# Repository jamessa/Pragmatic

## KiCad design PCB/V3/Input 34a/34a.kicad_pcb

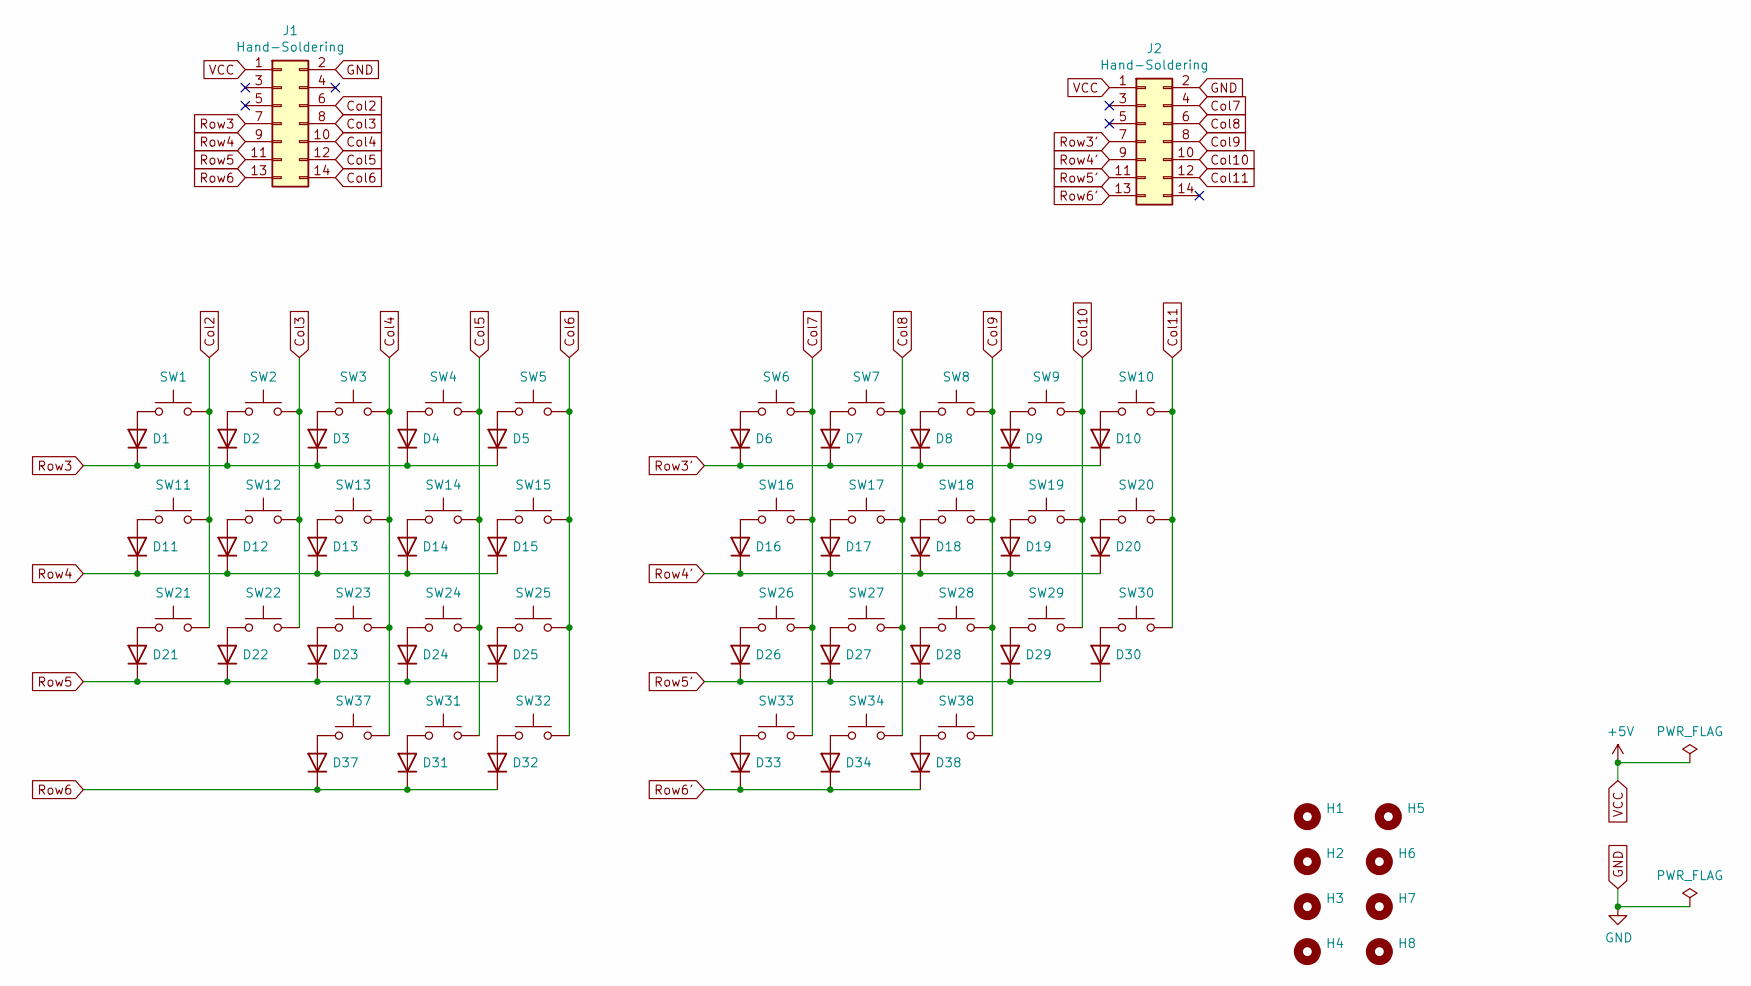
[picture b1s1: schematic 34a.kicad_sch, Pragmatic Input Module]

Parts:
D1, D2, D3, D4, D5, D6, D7, D8, D9, D10, D11, D12, D13, D14, D15, D16, D17, D18, D19, D20, D21, D22, D23, D24, D25, D26, D27, D28, D29, D30, D31, D32, D33, D34, D37, D38: 1N4148; D3_SMD_v2; LCSC C81598
H1, H2, H3, H4, H5, H6, H7, H8: MountingHole; MountingHole_2.5mm
J1, J2: Hand-Soldering; IDC-Header_2x07_P2.54mm_Vertical; LCSC C3406
SW1, SW2, SW3, SW4, SW5, SW6, SW7, SW8, SW9, SW10, SW11, SW12, SW13, SW14, SW15, SW16, SW17, SW18, SW19, SW20, SW21, SW22, SW23, SW24, SW25, SW26, SW27, SW28, SW29, SW30, SW31, SW32, SW33, SW34, SW37, SW38: SW_Push; MX_Hotswap

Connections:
Col2: J1.6, SW1.2, SW11.2, SW21.2
Col3: J1.8, SW2.2, SW12.2, SW22.2
Col4: J1.10, SW3.2, SW13.2, SW23.2, SW37.2
Col5: J1.12, SW4.2, SW14.2, SW24.2, SW31.2
Col6: J1.14, SW5.2, SW15.2, SW25.2, SW32.2
Col7: J2.4, SW6.2, SW16.2, SW26.2, SW33.2
Col8: J2.6, SW7.2, SW17.2, SW27.2, SW34.2
Col9: J2.8, SW8.2, SW18.2, SW28.2, SW38.2
Col10: J2.10, SW9.2, SW19.2, SW29.2
Col11: J2.12, SW10.2, SW20.2, SW30.2
GND: J1.2, J2.2
unnamed: D1.2 (A), SW1.1
unnamed: D2.2 (A), SW2.1
unnamed: D3.2 (A), SW3.1
unnamed: D4.2 (A), SW4.1
unnamed: D5.2 (A), SW5.1
unnamed: D6.2 (A), SW6.1
unnamed: D7.2 (A), SW7.1
unnamed: D8.2 (A), SW8.1
unnamed: D9.2 (A), SW9.1
unnamed: D10.2 (A), SW10.1
unnamed: D11.2 (A), SW11.1
unnamed: D12.2 (A), SW12.1
unnamed: D13.2 (A), SW13.1
unnamed: D14.2 (A), SW14.1
unnamed: D15.2 (A), SW15.1
unnamed: D16.2 (A), SW16.1
unnamed: D17.2 (A), SW17.1
unnamed: D18.2 (A), SW18.1
unnamed: D19.2 (A), SW19.1
unnamed: D20.2 (A), SW20.1
unnamed: D21.2 (A), SW21.1
unnamed: D22.2 (A), SW22.1
unnamed: D23.2 (A), SW23.1
unnamed: D24.2 (A), SW24.1
unnamed: D25.2 (A), SW25.1
unnamed: D26.2 (A), SW26.1
unnamed: D27.2 (A), SW27.1
unnamed: D28.2 (A), SW28.1
unnamed: D29.2 (A), SW29.1
unnamed: D30.2 (A), SW30.1
unnamed: D31.2 (A), SW31.1
unnamed: D32.2 (A), SW32.1
unnamed: D33.2 (A), SW33.1
unnamed: D34.2 (A), SW34.1
unnamed: D37.2 (A), SW37.1
unnamed: D38.2 (A), SW38.1
Row3: D1.1 (K), D2.1 (K), D3.1 (K), D4.1 (K), D5.1 (K), J1.7
Row3': D6.1 (K), D7.1 (K), D8.1 (K), D9.1 (K), D10.1 (K), J2.7
Row4: D11.1 (K), D12.1 (K), D13.1 (K), D14.1 (K), D15.1 (K), J1.9
Row4': D16.1 (K), D17.1 (K), D18.1 (K), D19.1 (K), D20.1 (K), J2.9
Row5: D21.1 (K), D22.1 (K), D23.1 (K), D24.1 (K), D25.1 (K), J1.11
Row5': D26.1 (K), D27.1 (K), D28.1 (K), D29.1 (K), D30.1 (K), J2.11
Row6: D31.1 (K), D32.1 (K), D37.1 (K), J1.13
Row6': D33.1 (K), D34.1 (K), D38.1 (K), J2.13
VCC: J1.1, J2.1

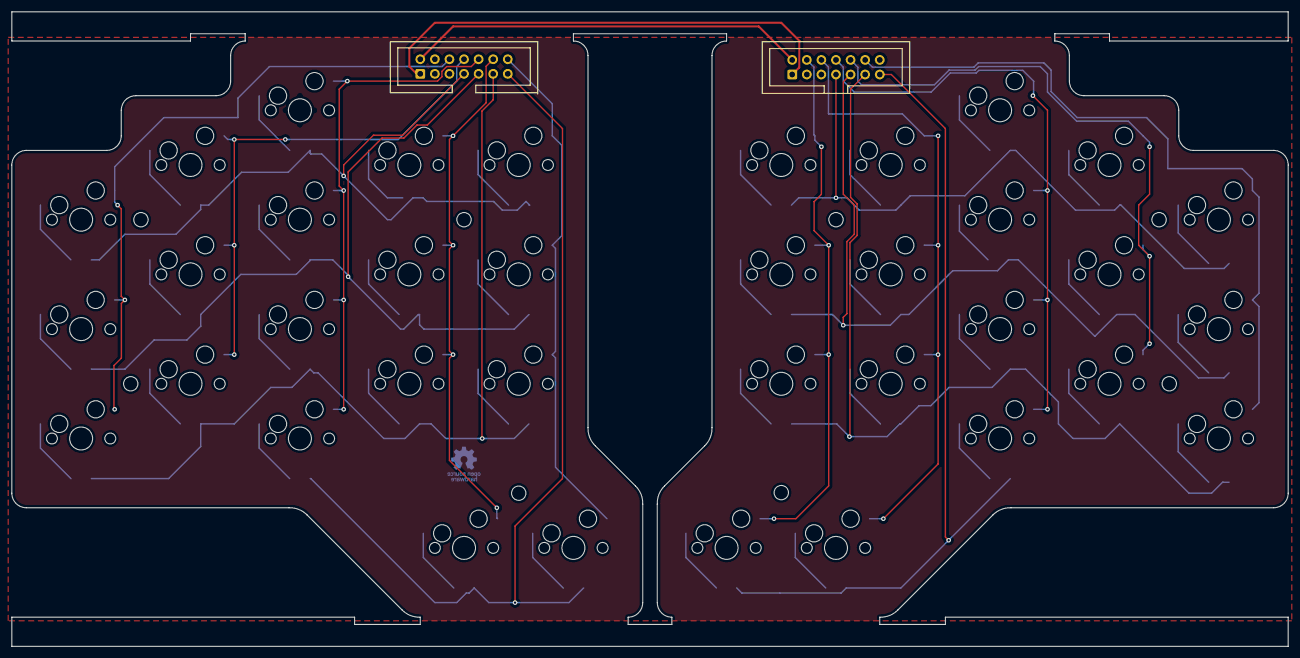
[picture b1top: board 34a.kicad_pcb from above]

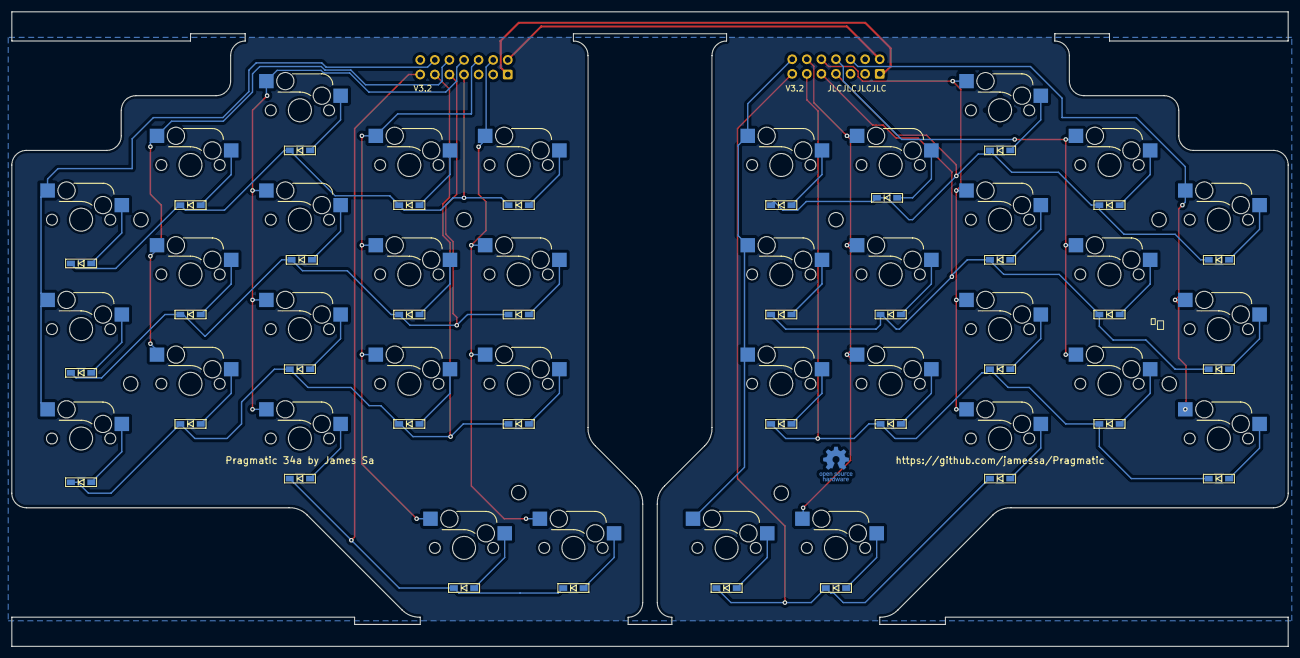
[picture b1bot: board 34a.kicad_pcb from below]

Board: 2 copper layers, 222.2 x 110.5 mm, 83 parts (37 on the bottom side), 56 nets.

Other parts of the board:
LOGO1: Logo_Open_Hardware_Small; OSHW-Logo_5.7x6mm_Copper

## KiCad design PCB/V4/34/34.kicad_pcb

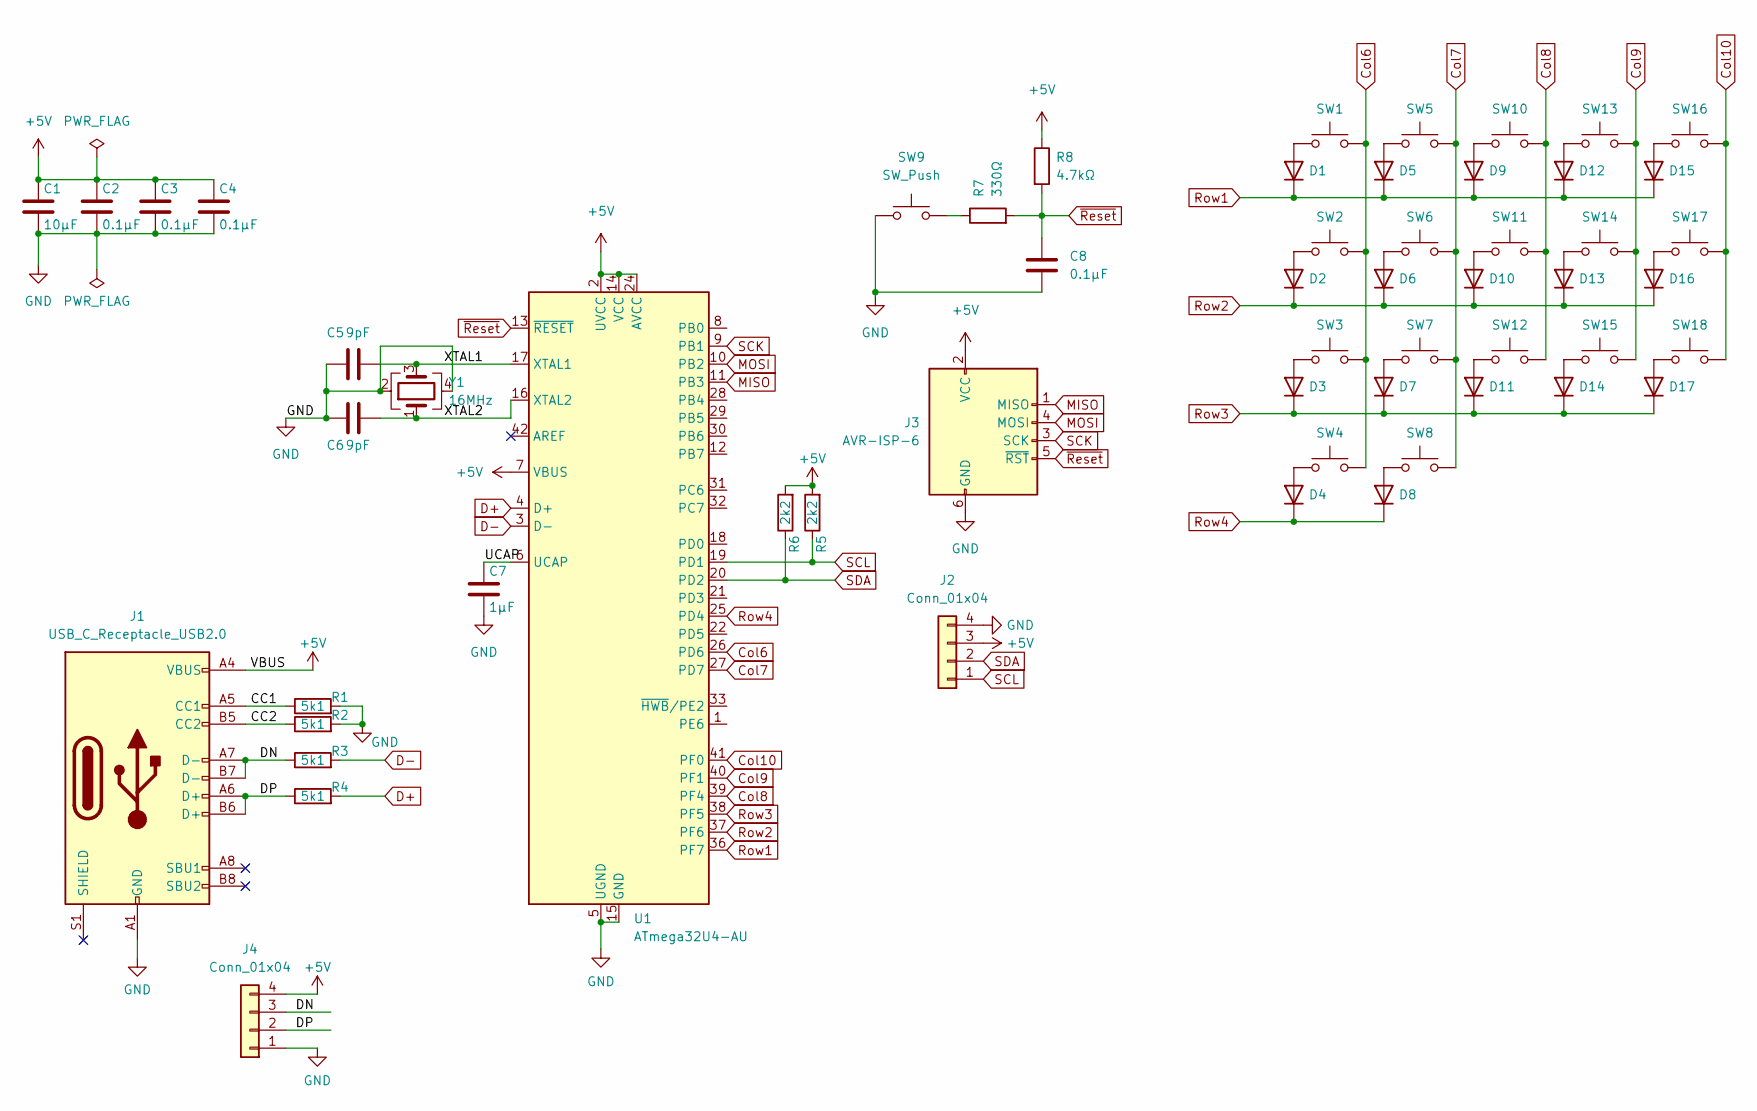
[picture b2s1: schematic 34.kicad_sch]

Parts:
C1: 10µF; C_0603_1608Metric_Pad1.08x0.95mm_HandSolder
C2, C3, C4, C8: 0.1µF; C_0402_1005Metric_Pad0.74x0.62mm_HandSolder
C5, C6: 9pF; C_0402_1005Metric_Pad0.74x0.62mm_HandSolder
C7: 1µF; C_0402_1005Metric_Pad0.74x0.62mm_HandSolder
D1, D2, D3, D4, D5, D6, D7, D8, D9, D10, D11, D12, D13, D14, D15, D16, D17: 1N4148; D3_SMD_v2; LCSC C81598
J1: USB_C_Receptacle_USB2.0; USB_C_Receptacle_HRO_TYPE-C-31-M-12; LCSC C165948
J2: Conn_01x04; JST_PH_S4B-PH-K_1x04_P2.00mm_Horizontal; LCSC C265452
J3: AVR-ISP-6; PinHeader_2x03_P2.54mm_Vertical
J4: Conn_01x04; USB wire pad
R1, R2, R3, R4: 5k1; R_0402_1005Metric_Pad0.72x0.64mm_HandSolder
R5, R6: 2k2; R_0402_1005Metric_Pad0.72x0.64mm_HandSolder
R7: 330Ω; R_0402_1005Metric_Pad0.72x0.64mm_HandSolder
R8: 4.7kΩ; R_0402_1005Metric_Pad0.72x0.64mm_HandSolder
SW1, SW2, SW3, SW4, SW5, SW6, SW7, SW8, SW10, SW11, SW12, SW13, SW14, SW15, SW16, SW17, SW18: SW_Push; MX_Hotswap_Choc_Solder
SW9: SW_Push; SW_SPST_SKQG_WithStem
U1: ATmega32U4-AU; TQFP-44_10x10mm_P0.8mm
Y1: 16MHz; Crystal_SMD_3225-4Pin_3.2x2.5mm; LCSC C13738

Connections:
+5V: C1.1, C2.1, C3.1, C4.1, J1.A4 (VBUS), J1.A9 (VBUS), J1.B4 (VBUS), J1.B9 (VBUS), J2.3, J3.2 (VCC), J4.4, R5.2, R6.2, R8.1, U1.2 (UVCC), U1.7 (VBUS), U1.14 (VCC), U1.24 (AVCC), U1.34 (VCC), U1.44 (AVCC)
/CC1: J1.A5 (CC1), R1.1
/CC2: J1.B5 (CC2), R2.1
/DN: J1.A7 (D-), J1.B7 (D-), J4.3, R3.1
/DP: J1.A6 (D+), J1.B6 (D+), J4.2, R4.1
/UCAP: C7.1, U1.6 (UCAP)
/XTAL1: C5.2, U1.17 (XTAL1), Y1.3
/XTAL2: C6.2, U1.16 (XTAL2), Y1.1
Col6: SW1.2, SW2.2, SW3.2, SW4.2, U1.26 (PD6)
Col7: SW5.2, SW6.2, SW7.2, SW8.2, U1.27 (PD7)
Col8: SW10.2, SW11.2, SW12.2, U1.39 (PF4)
Col9: SW13.2, SW14.2, SW15.2, U1.40 (PF1)
Col10: SW16.2, SW17.2, SW18.2, U1.41 (PF0)
D+: R4.2, U1.4 (D+)
D-: R3.2, U1.3 (D-)
GND: C1.2, C2.2, C3.2, C4.2, C5.1, C6.1, C7.2, C8.2, J1.A1 (GND), J1.A12 (GND), J1.B1 (GND), J1.B12 (GND), J2.4, J3.6 (GND), J4.1, R1.2, R2.2, SW9.1, U1.5 (UGND), U1.15 (GND), U1.23 (GND), U1.35 (GND), U1.43 (GND), Y1.2, Y1.4
MISO: J3.1 (MISO), U1.11 (PB3)
MOSI: J3.4 (MOSI), U1.10 (PB2)
unnamed: D1.2 (A), SW1.1
unnamed: D2.2 (A), SW2.1
unnamed: D3.2 (A), SW3.1
unnamed: D4.2 (A), SW4.1
unnamed: D5.2 (A), SW5.1
unnamed: D6.2 (A), SW6.1
unnamed: D7.2 (A), SW7.1
unnamed: D8.2 (A), SW8.1
unnamed: D9.2 (A), SW10.1
unnamed: D10.2 (A), SW11.1
unnamed: D11.2 (A), SW12.1
unnamed: D12.2 (A), SW13.1
unnamed: D13.2 (A), SW14.1
unnamed: D14.2 (A), SW15.1
unnamed: D15.2 (A), SW16.1
unnamed: D16.2 (A), SW17.1
unnamed: D17.2 (A), SW18.1
unnamed: R7.1, SW9.2
Row1: D1.1 (K), D5.1 (K), D9.1 (K), D12.1 (K), D15.1 (K), U1.36 (PF7)
Row2: D2.1 (K), D6.1 (K), D10.1 (K), D13.1 (K), D16.1 (K), U1.37 (PF6)
Row3: D3.1 (K), D7.1 (K), D11.1 (K), D14.1 (K), D17.1 (K), U1.38 (PF5)
Row4: D4.1 (K), D8.1 (K), U1.25 (PD4)
SCK: J3.3 (SCK), U1.9 (PB1)
SCL: J2.1, R6.1, U1.19 (PD1)
SDA: J2.2, R5.1, U1.20 (PD2)
~Reset: C8.1, J3.5 (~RST), R7.2, R8.2, U1.13 (~RESET)

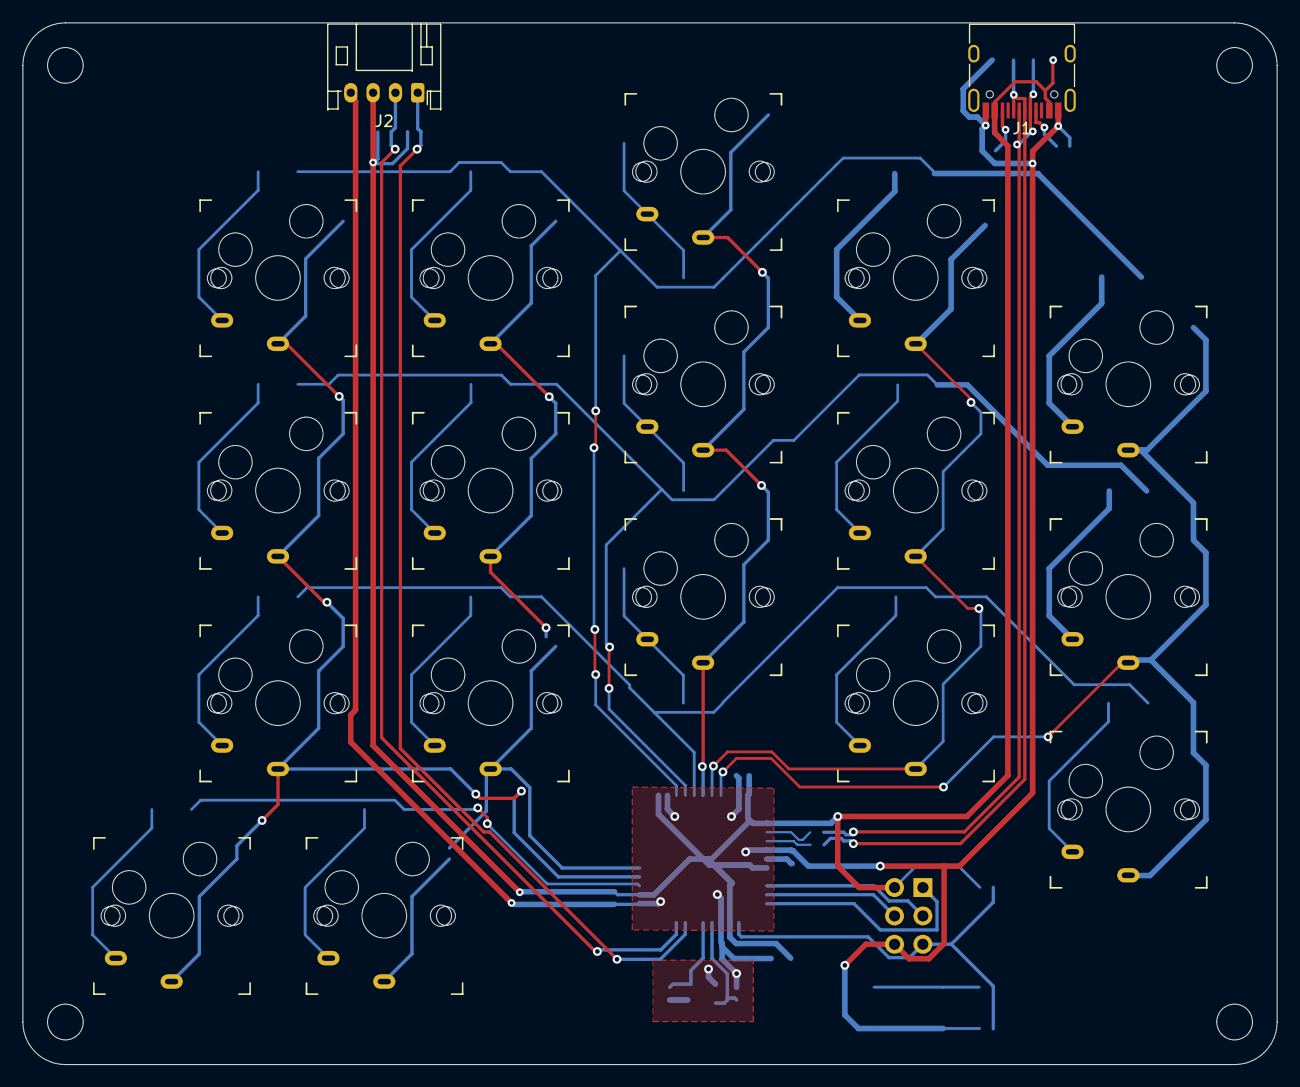
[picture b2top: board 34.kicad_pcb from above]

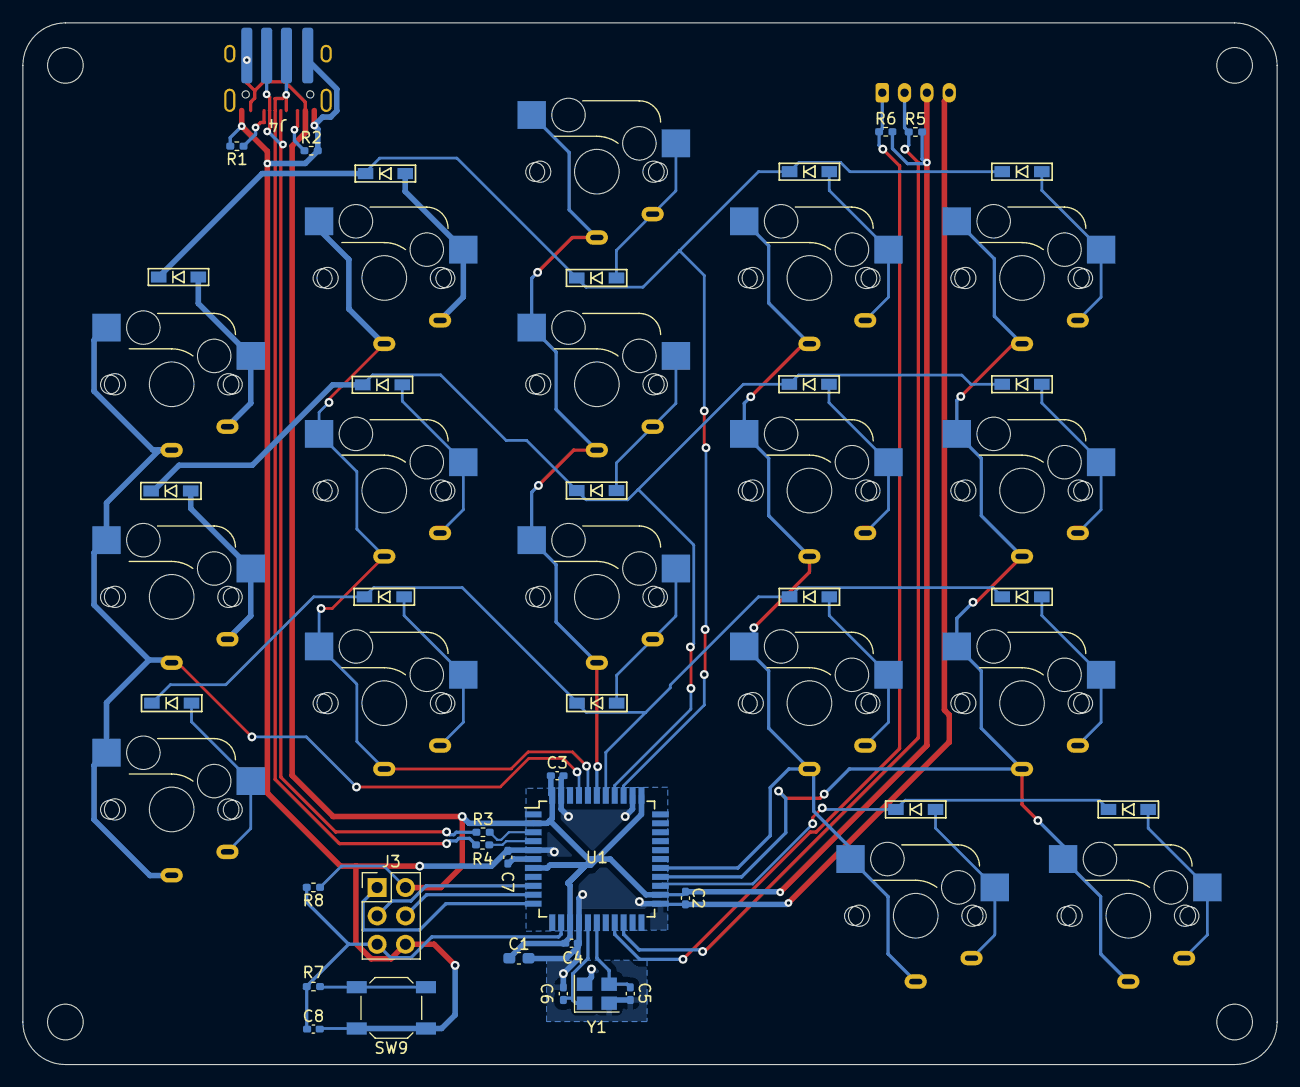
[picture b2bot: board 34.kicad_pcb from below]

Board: 2 copper layers, 112.4 x 93.3 mm, 57 parts (38 on the bottom side), 44 nets.
